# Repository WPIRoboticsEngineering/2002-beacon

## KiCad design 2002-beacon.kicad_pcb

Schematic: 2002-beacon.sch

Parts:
C1, C3: C; CP_Radial_D5.0mm_P2.00mm
D1, D3: LED; LED_D3.0mm_Horizontal_O3.81mm_Z6.0mm
D2: LED; LED_D3.0mm
H1, H2, H3, H4: MountingHole; MountingHole_3.2mm_M3
J1: USB_B; USB_Micro-B_Molex-105017-0001
Q1, Q2: 2N3904; TO-92_Inline
R1, R5: 470; R_Axial_DIN0204_L3.6mm_D1.6mm_P7.62mm_Horizontal
R2: 2k; R_Axial_DIN0204_L3.6mm_D1.6mm_P7.62mm_Horizontal
R3, R4: 74; R_Axial_DIN0204_L3.6mm_D1.6mm_P7.62mm_Horizontal
SW1: SW_SPST; SW_PUSH_6mm
U2: ATtiny85-20PU; DIP-8_W7.62mm

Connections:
+5V: C1.1, C3.2, D1.2 (A), D3.2 (A), J1.1, U2.8
GND: C1.2, C3.1, D2.1 (K), J1.4, J1.5, Q1.1 (E), Q2.1 (E), SW1.2 (B), U2.4
unnamed: D1.1 (K), R3.2
unnamed: D2.2 (A), R2.1
unnamed: D3.1 (K), R4.2
unnamed: Q1.2 (B), R1.1
unnamed: Q1.3 (C), R3.1
unnamed: Q2.2 (B), R5.1
unnamed: Q2.3 (C), R4.1
unnamed: R1.2, R5.2, U2.6
unnamed: R2.2, U2.3
unnamed: SW1.1 (A), U2.2

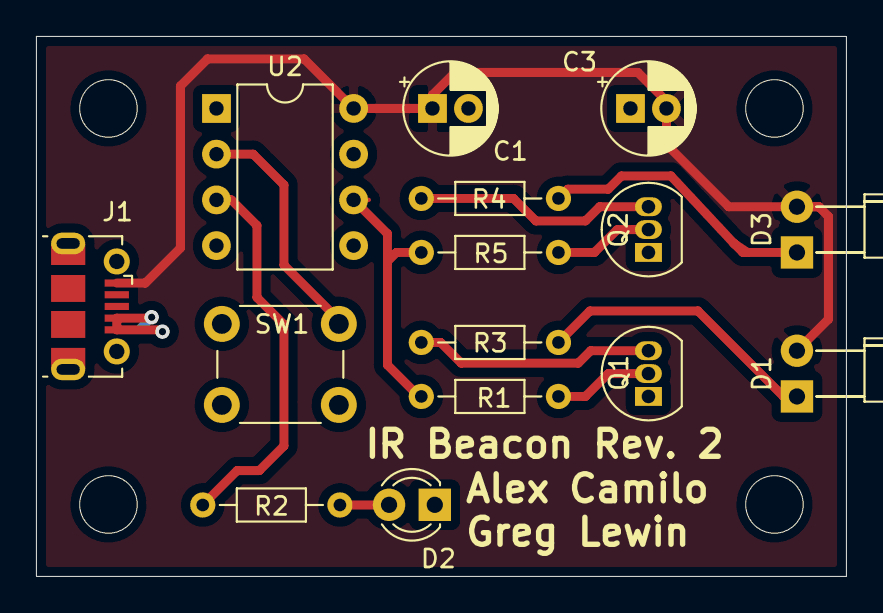
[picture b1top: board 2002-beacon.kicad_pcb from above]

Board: 2 copper layers, 45.0 x 30.0 mm, 19 parts (0 on the bottom side), 12 nets.

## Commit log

2019-11-20 fixed routing
2020-02-26 Layout for rev2 done
2020-02-26 some cleanup of traces, clenup silk, add board ver and authors
2020-03-02 Added MFN and MPN info
